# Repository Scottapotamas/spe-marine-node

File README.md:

# Underwater Sensor Node with Single Pair Ethernet
Prototype project to build a underwater sensor node, powered by and communicating with the surface via Single Pair Ethernet (10BASE-T1L + 802.3cg Type E Class 10-12).

A more detailed write-up can be [read on Electric UI's blog](https://electricui.com/blog/spe-sensor-node).

# Mechanical

## Housing

The body of the sensor node is a 2″ acrylic tube (*~58mm OD*), with a pair of aluminium end-caps. This provides a working volume constrained by the 50 mm internal diameter and ~118 mm maximum gap between caps.

The top cap/bulkhead has 4×M10 threaded holes for accessories as part of BlueRobotic's hardware ecosystem. The assembled prototype is fitted with:

- 4.5mm Wetlink penetrator for the tether cable
- 10m rated pressure sensor
- White indicator LED
- Pressure relief/test valve

Whilst this prototype won't see properly deep water, this tube arrangement should be capable of  200m operation, and far deeper if an aluminium sleeve is used.

CAD models and assemblies are in `/mechanical/tube/`. Off-the-shelf parts are in `/mechanical/tube/cots/`.

## Internal brackets

A pair of 3D printed board mounts use the 4×M3 internal mounting holes in the bulkheads.

CAD models and STL files are in `/mechanical/tube/`. 

## Mounting

The tube itself doesn't have any features for mounting, so a pair of custom tube clamps were printed with the general goal of providing generic strap or wire mounting points. 

Files are in `/mechanical/mount/`.

# Electronics

Compatibility with the [Sparkfun MicroMod ecosystem](https://www.sparkfun.com/micromod) has been maintained where possible - building off of [Sparkfun's ADIN1110 function board](https://www.sparkfun.com/products/19038) for bring-up and early software tests.

PCB's were designed with KiCAD 7. Project files, gerbers and schematic PDF's are in `/electronics/`.

A small collection of calculator spreadsheets were made to help during the design process - these are in `/docs` and use Open Office `.ods` format.

Version 1.0 boards do have some minor issues which were tweaked during bench testing, so I'd recommend reviewing things thorough before copying anything into your designs.

## Backplane

Acting as the MicroMod 'carrier', providing the processor and function board connections, as well as regulation, I2C headers, and breakout pads for spare/conflicted IO. It also serves as the mounting interface for sensor payloads and custom hardware. 

It's a 46×100 mm 1.6 mm 2-layer board with pretty relaxed fabrication requirements. 

## PD and PSE Function Boards

Both boards implement the ADIN1110 SPE transceiver in a similar manner to Sparkfun's function board, but exist as two variants which improve over the dev-kit by adding:

- Circuitry to act as a Class 10-12 PoDL **power supply** aka PSE (pictured below on left).

- VID circuitry to signal compliance as a Class 10-12 PoDL **powered device** aka PD (pictured on right).

> These boards only provide detection, not classification via SCCP, and as such runs in 'fast-start mode'.

The PCB's are A×B mm, 0.8mm thick, 2-layer boards which can be manufactured with commodity fabs. I just used the raw straight PCB edge-connector without issues, but for best practice and/or frequent insertion cycles the edge-connector should be bevelled.

The blog post describes PoDL circuit behaviour and integration in more detail.

## Sensors

The project was designed without assuming any specific sensors would be used, but I used these I2C sensors:

- Temperature & Humidity - `SHTC3` via [Sparkfun `SEN-16467`](https://www.sparkfun.com/products/16467)
- Motion - `LSM6DSO` via [Sparkfun `SEN-18020`](https://www.sparkfun.com/products/18020)
- Depth/Pressure - `MS5837` via [BlueRobotics `Bar02`](https://bluerobotics.com/store/sensors-cameras/sensors/bar02-sensor-r1-rp/)

# Firmware

I used an ESP32 MicroMod processor board along with the Arduino toolchain. As such, there are external dependencies on the ESP32 Arduino core, [`electricui-embedded`](https://github.com/electricui/electricui-embedded), and Sparkfun packages for their [ESP32 boards](https://github.com/sparkfun/Arduino_Boards), [`LSM6DS0`](https://github.com/sparkfun/SparkFun_Qwiic_6DoF_LSM6DSO), [`SHTC3`](https://github.com/sparkfun/SparkFun_SHTC3_Arduino_Library) and [`ADIN1110`](https://github.com/sparkfun/SparkFun_ADIN1110_Arduino_Library) libraries.

I also depend on my own [`MS5837`](https://github.com/Scottapotamas/MS5837) library (external to this repo) for working with the pressure sensor.

The `/firmware` folder has some of the test-sketches written during testing:

- `spe-pse-io` - Bench-test PoDL PSE behaviour with a simple state-machine
- `lsm6ds0-fifo-test` - Configures and reads IMU samples periodically from the buffer
- `led-io-test` - Rough test using Pololu's APA102 library to check the 2×24 LED rings
- `spe-eui-bridge` - Transparent proxy of `electricui-embedded` packets with ADIN1110 raw buffers to serial ports.

> These sketches weren't written to act as examples or as reference material, and should be treated accordingly.

The main firmware is actually rather straightforward, running a superloop which runs each sub-system at a defined rate. Sub-systems never block, and are generally only responsible for their own behaviour. 

> **TODO: Cleanup and merge branches/sources into this repo**

# User Interface

> **TODO: Cleanup and merge sources into this repo**

The user interface is built with [Electric UI](https://electricui.com), and can be built and run by invoking `arc start` from `/interface`.

It handles visualisation of data streaming off the sensor node, and provides additional statistics and logging.

**TODO: Write part 2 post on data processing and visualisation**

# Additional Notes

_If_ you're planning on replicating this project, or part of it, some additional points of interest:

- I'm happy to answer questions or help with design changes to suit your ocean research project.
  - I'm also generally open to consulting work!
- Firmware is pretty specific to my own tooling and relies on external libraries for sensors and the Arduino ESP32 core.
- Read over BlueRobotics's guides for Wetlink penetrator use, enclosure assembly, pressure testing.
  - Definitely do remember to lubricate o-rings and the tube bulkheads as you slide them into the cylinder. It's _very difficult_ to get them out dry... 
- The tube *as designed and pictured* is positively buoyant and might need additional ballast weight depending on your application and safety requirements around handling.

Its also worth mentioning that the entire detailed conceptualisation, design, ordering, assembly, testing and writeup occurred in August 2023. There were many late nights, and as a result some design choices were made with simplicity or time-frame in mind.

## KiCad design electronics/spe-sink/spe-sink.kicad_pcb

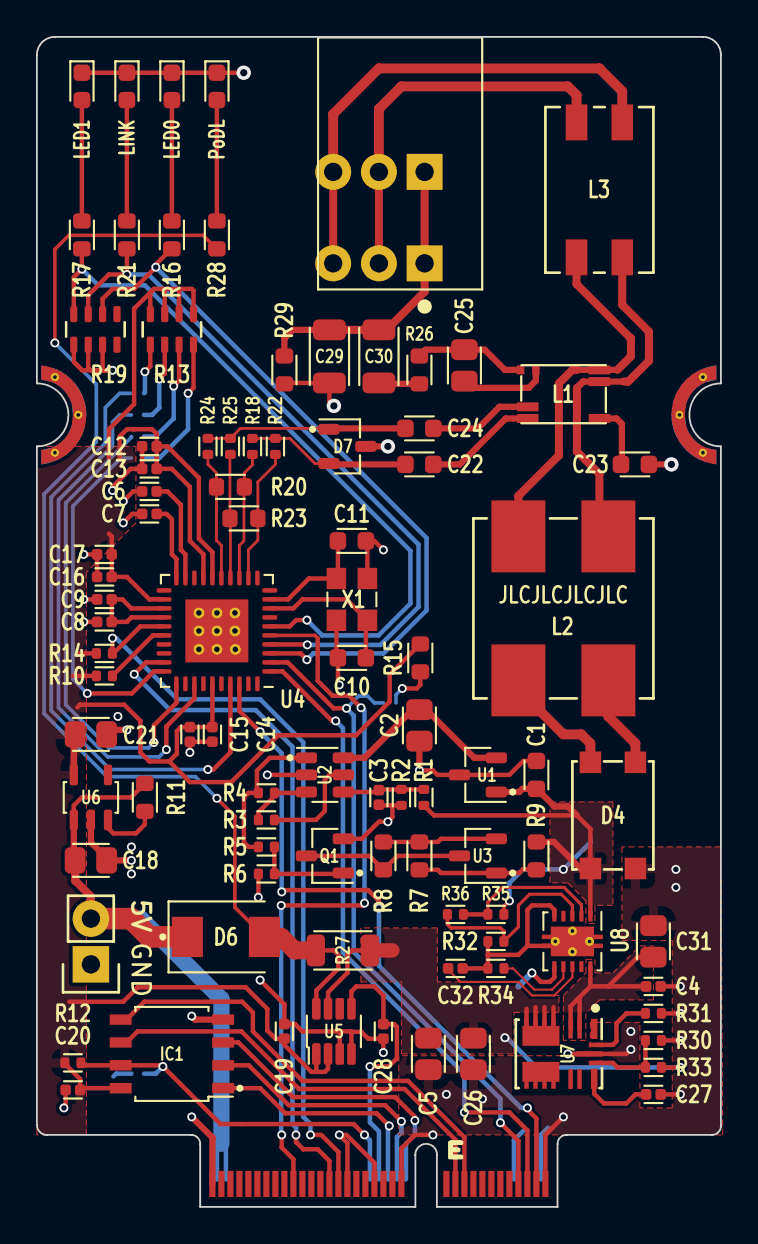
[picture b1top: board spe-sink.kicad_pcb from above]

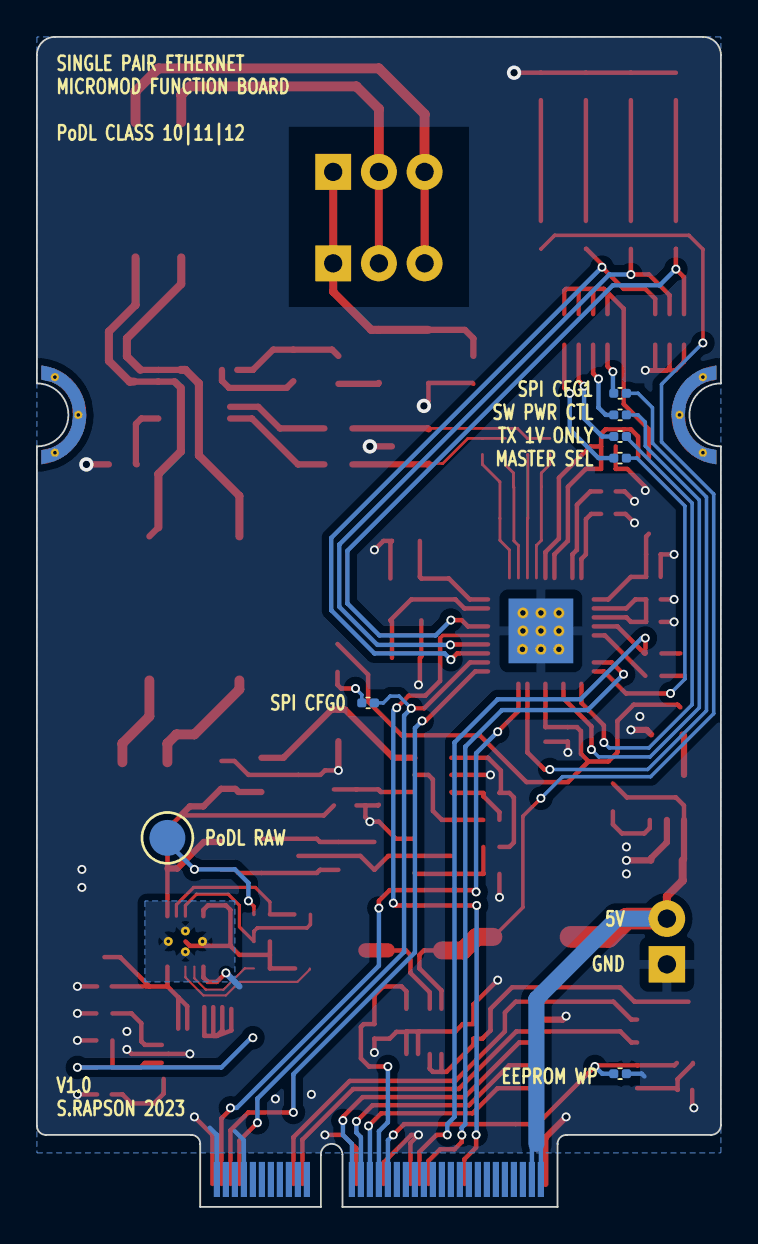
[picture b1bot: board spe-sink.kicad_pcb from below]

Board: 2 copper layers, 38.0 x 65.0 mm, 99 parts (7 on the bottom side), 79 nets.

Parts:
C1: 56n_X7R_1608M; CAPC1608X90N
C2, C18, C21: 10u_X7R_2012M; CAPC2012X110N
C3: 330p_X7R_1005M; CAPC1005X60N
C4, C6, C8, C12, C14, C16, C19, C20: 100n_X7R_1005M; CAPC1005X60N
C5, C26: 22u_X5R_2012M; CAPC2012X110N
C7, C27: 1u_X5R_1005M; CAPC1005X60N
C9: 470n_X5R_1005M; CAPC1005X60N
C10, C11: 22p_X7R_1608M; CAPC1608X90N
C13, C15, C17, C32: 10n_X7R_1005M; CAPC1005X60N
C22, C24: 220n_X7R_1608M; CAPC1608X90N
C23: 100n_X7R_1608M; CAPC1608X90N
C25: 470n_X7R_2012M_100V; CAPC2012X110N
C28: 1n_X7R_1005M; CAPC1005X60N
C29, C30: 1n_X7R_3216M_2kV; CAPC3216X135N
C31: 10u_X5R_2012M_50V; CAPC2012X110N
D1: LED_GREEN_1608M; LEDC1608X80L40N
D2: LED_YELLOW_1608M; LEDC1608X80L40N
D3: LED_BLUE_1608M; LEDC1608X80L40N
D4: CD-HD2006L; CD-HD2x(L)
D5: LED_RED_1608M; LEDC1608X80L40N
D6: B240Q-13-F; SODFL5436X262N
D7: D1213A; SOT95P240X110-3L16N
IC1: AT24C02C-SSHM; SOIC127P600X330-8L2N
J1: CONN_01X05_RA; CUI_TBL009-254-03
L1: WE-STST_74930000; WE-STST
L2: COUPLED_47uH_1500mA_340mOhm; WE-MCRI-1040
L3: COMM_MODE_1000uH_800mA_0.3R; WE-SL2
P2: CONN_01X02; 61300211121
Q1: 2N7002P; SOT95P240X110-3L16N
R1: 1M_1005M; RESC1005X40N
R2, R4: 470K_1005M; RESC1005X40N
R3, R6, R30: 10K0_1005M; RESC1005X40N
R5: 0R_1005M; RESC1005X40N
R7: 9K09_1608M; RESC1608X50N
R8: 20K0_1608M; RESC1608X50N
R9: 22R_1608M; RESC1608X50N
R10, R14: 1K5_1005M; RESC1005X40N
R11: 10K0_1608M; RESC1608X50N
R12: 100K_1005M; RESC1005X40N
R13, R19: 4K7_QUAD_ARRAY_1608M; R_Array_Concave_4x1608M
R15: 4K7_1608M; RESC1608X50N
R16, R21, R28: 1K00_1608M; RESC1608X50N
R17: 2K40_1608M; RESC1608X50N
R18, R25: 5K1_1005M; RESC1005X40N
R20, R23: 10K2_1608M; RESC1608X50N
R22, R24: 49R9_1005M; RESC1005X40N
R26: 100R_1608M; RESC1608X50N
R27: R01_3216M; RESC3216X60N
R29: 1M_1608M; RESC1608X50N
R31: 15K_1005M; RESC1005X40N
R32: 26K1_1005M; RESC1005X40N
R33: 40K2_1005M; RESC1005X40N
R34: 13K_1005M; RESC1005X40N
R35: 680K_1005M; RESC1005X40N
R36: 36K_1005M; RESC1005X40N
SL2, SL3, SL4, SL5, SL6, SL7: SOLDER-LINK-2-TINY; SJ1005-2N
TEST1: PROBE_PAD; TP200
U1: AP7375-33; SOT95P240X110-3L16N
U2: MCP65R41T; SOT95P240X110-6L16N
U3: ATL431LIB; SOT95P240X110-3L16N
U4: ADIN1110; QFN50P600X600X100-40T350X350N
U5: INA186A3; SOT23-8P65_280X145L45X30N
U6: AP2112K-3.3; SOT95P280X145-5L30N
U7: TLVM23625RDNR; QFN50P450X350X200-11-FCMOD11
U8: TPS26625; SON50P300X300X90-11T240X165N_RELIEF
X1: RH100-25.000-13-F-0715; OSCCC320X250X60L90X100N
X2: MICROMOD_FUNCTION_BOARD_EDGE; M.2-MICROMOD-FN-CARD-EDGE

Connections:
+3.3V: C12.1, C13.1, C14.1, C15.1, C16.1, C17.1, C19.1, C20.1, C21.1, IC1.8 (VCC), R10.1, R12.1, R13.1, R13.2, R13.3, R13.4, R14.1, R15.1, U4.16 (AVDD_H), U4.17 (AVDD_H), U4.22 (AVDD_L), U4.35 (VDDIO), U5.1 (VCC), U5.2 (EN), U6.5 (VOUT)
+POWER: C18.1, D6.C, P2.2, R11.1, U6.1 (VIN), X2.72 (VCC), X2.74 (VCC)
/Ethernet MAC+PHY/CIPO: SL4.1, U4.2 (SDO/SPI_CFG0), X2.7 (SPI_SDO)
/Ethernet MAC+PHY/CLK: U4.38 (SCLK), X2.3 (SPI_SCK)
/Ethernet MAC+PHY/COPI: U4.1 (SDI), X2.5 (SPI_SDI)
/Ethernet MAC+PHY/DATA+: C24.2, D7.1 (A1), R24.1, R25.1
/Ethernet MAC+PHY/DATA-: C22.2, D7.2 (C2), R18.1, R22.1
/Ethernet MAC+PHY/~CS: U4.29 (~CS), X2.49 (F1/~CS)
/Ethernet MAC+PHY/~INT: R14.2, U4.25 (~INT), X2.47 (F0/~INT)
/Ethernet MAC+PHY/~RESET: U4.5 (~RESET), X2.57 (F5)
/MicroMod Function Board/ANALOG: C28.1, U5.5 (Vout), X2.38 (A0)
/MicroMod Function Board/SCL: IC1.6 (SCL), X2.21 (I2C_SCL)
/MicroMod Function Board/SDA: IC1.5 (SDA), X2.19 (I2C_SDA)
/PoDL Device Handling/PoDL+: C1.1, D4.1 (+), R1.1, R9.1, R35.1, TEST1.1 (PAD), U1.1 (VIN), U8.1 (IN)
Earth: C29.2, C30.1, J1.1, R29.1
GND: C1.2, C2.2, C3.2, C4.2, C5.2, C6.2, C7.2, C8.2, C9.2, C10.2, C11.2, C12.2, C13.2, C14.2, C15.2, C16.2, C17.2, C18.2, C19.2, C20.2, C21.2, C23.2, C26.2, C27.2, C28.2, C30.2, C31.2, D1.C, D2.C, D3.C, D4.4 (-), D5.C, D7.3, IC1.4 (GND), P2.1, Q1.2 (S), R2.2, R6.2, R19.1, R19.2, R19.3, R29.2, R30.2, R31.2, SL2.2, U1.3 (GND), U2.2 (V-), U4.41 (EP(GND)), U5.3 (REF), U5.4 (GND), U6.2 (GND), U7.10 (GND), U8.6 (GND), X1.2, X1.4, X2.1 (GND), X2.2 (GND), X2.8 (GND), X2.33 (GND), X2.39 (GND), X2.45 (GND), X2.75 (GND)
unnamed: C22.1, L1.1
unnamed: C23.1, L1.5
unnamed: C24.1, L1.2
unnamed: C25.1, L1.4
unnamed: C25.2, L1.3, R26.1
unnamed: C29.1, R26.2
unnamed: D1.A, R16.1
unnamed: D2.A, R17.1
unnamed: D3.A, R21.1
unnamed: D4.2 (∿), L2.4
unnamed: D4.3 (∿), L2.1
unnamed: D5.A, R28.2
unnamed: IC1.1 (A0), X2.36 (EEPROM_A0)
unnamed: IC1.2 (A1), X2.34 (EEPROM_A1)
unnamed: IC1.3 (A2), X2.32 (EEPROM_A2)
unnamed: IC1.7 (WP), R12.2, SL2.1, X2.40 (EEPROM_WP)
unnamed: J1.2, L3.2
unnamed: J1.3, L3.1
unnamed: L1.6, L2.2, L3.4
unnamed: L1.7, L2.3, L3.3
unnamed: Q1.3 (D), R8.2, U3.3 (A)
unnamed: Q1.1 (G), R5.2, R6.1
unnamed: R4.2, R5.1, U2.1
unnamed: R13.5, SL3.2
unnamed: R13.6, SL6.2
unnamed: R13.7, SL7.2
unnamed: R13.8, SL5.2
unnamed: R15.2, SL4.2
unnamed: C2.1, U1.2 (VOUT), U2.6 (V+)
unnamed: R3.2, R4.1, U2.3 (+)
unnamed: C3.1, R1.2, R2.1, U2.4 (-)
unnamed: R3.1, U2.5 (REF)
unnamed: R7.1, R9.2, U3.1 (C)
unnamed: R7.2, R8.1, U3.2 (REF)
unnamed: C6.1, U4.19 (CEXT_2)
unnamed: C7.1, U4.20 (CEXT_3)
unnamed: C8.1, C9.1, U4.23 (DLDO_1P1), U4.24 (DVDD_1P1)
unnamed: R16.2, R19.6, U4.3 (LED_0)
unnamed: R17.2, R19.8, U4.6 (LED_1)
unnamed: R19.7, R21.2, U4.4 (LINK_ST)
unnamed: R18.2, R20.1, U4.13 (RXN)
unnamed: R23.2, R25.2, U4.14 (RXP)
unnamed: SL3.1, U4.37 (SPI_CFG1)
unnamed: R10.2, U4.26 (TEST1)
unnamed: SL5.1, U4.30 (TS_TIMER/MS_SEL)
unnamed: R22.2, R23.1, U4.12 (TXN)
unnamed: R20.2, R24.2, U4.15 (TXP)
unnamed: C10.1, U4.8 (XTAL_I/CLK_IN), X1.3
unnamed: C11.1, U4.9 (XTAL_O), X1.1
unnamed: SL6.1, U4.33 (~SWPD_EN)
unnamed: SL7.1, U4.31 (~TX2P4_EN)
unnamed: C5.1, C26.1, R27.1, R33.1, U5.7 (S+), U7.4 (VOUT)
unnamed: D6.A, R27.2, R28.1, U5.8 (S-)
unnamed: R11.2, U6.3 (EN)
unnamed: C4.1, C31.1, U7.2 (EN), U7.3 (VIN), U8.10 (OUT)
unnamed: R30.1, R33.2, U7.9 (FB)
unnamed: R31.1, U7.11 (RT)
unnamed: C27.1, U7.8 (VCC)
unnamed: C32.2, R32.2, R34.2, U8.5 (RTN), U8.11 (EP)
unnamed: R34.1, U8.7 (ILIM)
unnamed: R32.1, R36.2, U8.3 (OVP)
unnamed: R35.2, R36.1, U8.2 (ULVO)
unnamed: C32.1, U8.8 (dVdT)

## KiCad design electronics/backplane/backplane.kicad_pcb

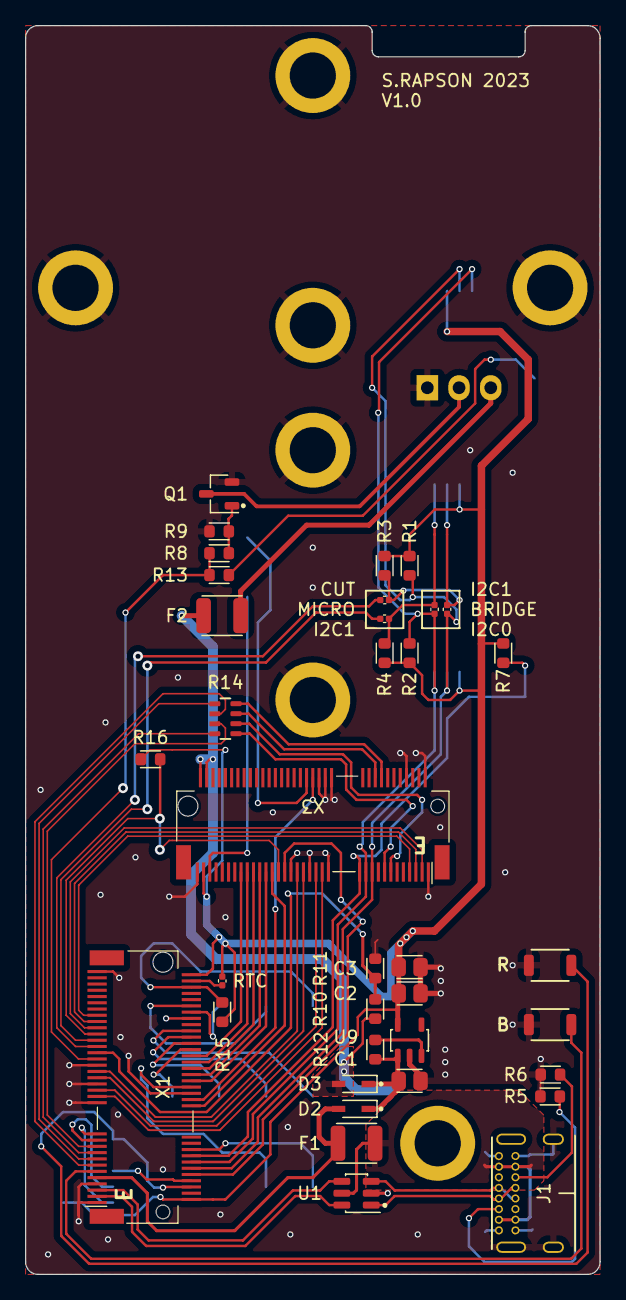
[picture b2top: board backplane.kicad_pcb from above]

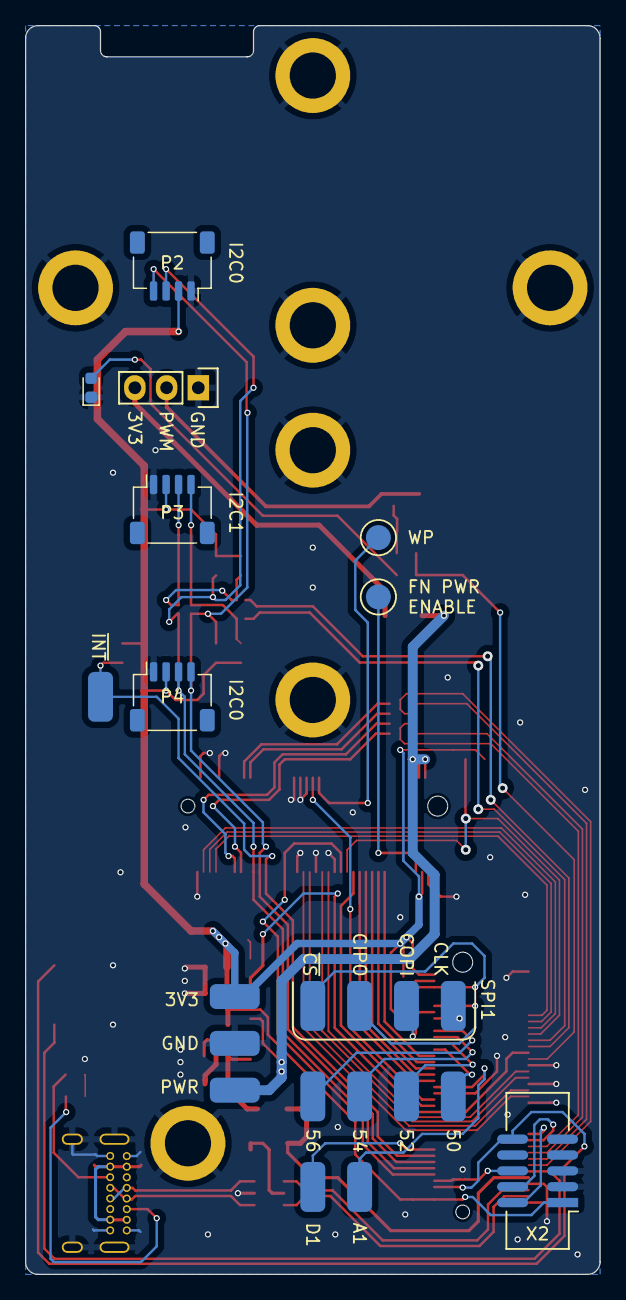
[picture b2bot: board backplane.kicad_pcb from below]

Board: 2 copper layers, 46.0 x 100.0 mm, 65 parts (26 on the bottom side), 68 nets.

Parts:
C1, C2, C3: 10u_X7R_2012M; CAPC2012X110N
D1: LED_YELLOW_1608M; LEDC1608X80L40N
D2, D3: 40V_500mA_SOD323; SOD2512X110N
F1, F2: 0.5A_1210L_PTC; FUSC3225X85L50N
J1: USB_C_SOCKET_RA_PTH_SIMPLE; USB_C_PTH_GCT_USB4085
MNT1, MNT2, MNT3: M2.5_SMD_2.5MM_THREADED; 9774025151R
MNT4, MNT5, MNT6, MNT7: M2.5_SMD_4.0MM_THREADED; 9774040151R
P1, P5, P6, P7, P8, P9, P11, P12, P13, P14, P15, P16, P17, P18: PAD_SOLDER_2mm
P2, P3, P4: JST_SH_4_RA; SM04B-SRSS-TB
P10: CONN_01X03; 61300311121
Q1: 2N7002P; SOT95P240X110-3L16N
R1, R2, R3, R4: 4K7_1608M; RESC1608X50N
R5, R6: 4K99_1608M; RESC1608X50N
R7, R9, R11, R12: 10K0_1608M; RESC1608X50N
R8: 10R_1608M; RESC1608X50N
R10: 20K0_1608M; RESC1608X50N
R13: 1K00_1608M; RESC1608X50N
R14: 0R_QUAD_ARRAY_1608M; R_Array_Concave_4x1608M
R15, R16: 100K_1608M; RESC1608X50N
SL1, SL4, SL5, SL6, SL7: SOLDER-LINK-2-TINY; SJ1005-2N
SW1, SW2: B3U-1000P_SPST-NO_SMD; B3U-1000P
TEST1, TEST2: PROBE_PAD; TP200
U1: USBLC6; SOT95P280X145-6L50N
U9: AP2112K-3.3; SOT95P280X145-5L30N
X1: MICROMOD_PROCESSOR_SOCKET; TE_2199230-4
X2: SWD_SMT_SOCKET; CNCTECH_3220-10-0300-00
X3: MICROMOD_FUNCTION_BOARD_SOCKET; TE_2199230-4

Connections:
+3.3V: C2.1, C3.1, P2.2, P3.2, P4.2, P15.1, R1.1, R2.1, R3.1, R4.1, R7.1, R15.1, R16.1, SL1.2, U9.5 (VOUT), X1.2 (3V3), X1.74 (3V3), X2.1 (VTref), X3.73 (3V3)
+POWER: D3.A, F2.1, P5.1, R10.1, X3.72 (VCC), X3.74 (VCC)
/Expansion IO/ANALOG_IN: P18.1, X1.38 (A1)
/Expansion IO/CIPO: P12.1, X1.64 (SPI_CIPO1/SDIO_DATA0)
/Expansion IO/CLK: P11.1, X1.60 (SPI_SCK1/SDIO_CLK)
/Expansion IO/COPI: P13.1, X1.62 (SPI_COPI1/SDIO_CMD)
/Expansion IO/DIGITAL_OUT: P17.1, X1.18 (D1/CAM_TRIG)
/Expansion IO/I2C0.SCL: P2.4, P4.4, R2.2, SL6.1, X1.14 (I2C_SCL), X3.21 (I2C_SCL)
/Expansion IO/I2C0.SDA: P2.3, P4.3, R1.2, SL7.2, X1.12 (I2C_SDA), X3.19 (I2C_SDA)
/Expansion IO/I2C1.SCL: P3.4, R4.2, SL5.1, SL6.2
/Expansion IO/I2C1.SDA: P3.3, R3.2, SL4.1, SL7.1
/Expansion IO/PWM_OUTPUT: R8.1, R13.2, X1.47 (PWM1)
/Expansion IO/~CS: P14.1, R15.2, X1.70 (~SPI_CS1/SDIO_DATA3)
/Expansion IO/~I2C_INT: P1.1, R7.2, X1.16 (~I2C_INT), X3.23 (~I2C_INT)
/Function Board/CAN.RX: X1.41 (CAN_RX), X3.41 (CAN_TX)
/Function Board/CAN.TX: X1.43 (CAN_TX), X3.43 (CAN_RX)
/Function Board/CIPO: X1.61 (SPI_CIPO), X3.7 (SPI_SDO)
/Function Board/CLK: X1.57 (SPI_SCK), X3.3 (SPI_SCK)
/Function Board/COPI: X1.59 (SPI_COPI), X3.5 (SPI_SDI)
/Function Board/CTS: R14.5, X1.15 (UARTCTS1)
/Function Board/D+: X1.35 (USBHOST_D+), X3.35 (USBHOST_D+)
/Function Board/D-: X1.37 (USBHOST_D-), X3.37 (USBHOST_D-)
/Function Board/FN_ANALOG: X1.34 (A0), X3.38 (A0)
/Function Board/FN_PWM: X1.32 (PWM0), X3.51 (F2/PWM)
/Function Board/FN_~INT: X1.10 (D0), X3.47 (F0/~INT)
/Function Board/G0: X1.40 (G0/BUS0), X3.53 (F3)
/Function Board/G1: X1.42 (G1/BUS1), X3.55 (F4)
/Function Board/G2: X1.44 (G2/BUS2), X3.57 (F5)
/Function Board/G3: X1.46 (G3/BUS3), X3.59 (F6)
/Function Board/G4: X1.48 (G4/BUS4), X3.61 (F7)
/Function Board/RTS: R14.6, X1.13 (UART_RTS1)
/Function Board/RX: R14.7, X1.19 (UART_RX1)
/Function Board/TX: R14.8, X1.17 (UART_TX1)
/Function Board/~CS: R16.2, X1.55 (~SPI_CS), X3.49 (F1/~CS)
/Power Regulation/USB_VCC: D2.A, F1.2, X1.9 (USB_VIN)
/Processor/NATIVE.D+: U1.6 (OUT_1), X1.3 (USB_D+)
/Processor/NATIVE.D-: U1.4 (OUT_2), X1.5 (USB_D-)
/Processor/SWDCLK: X1.21 (SWDCLK), X2.4 (SWCLK)
/Processor/SWDIO: X1.23 (SWDIO), X2.2 (SWDIO)
/Processor/SWO: X1.8 (G11/SWDSWO), X2.6 (SWO)
/Processor/~BOOT: SW2.1, X1.11 (BOOT)
/Processor/~RESET: SW1.1, X1.6 (~RESET), X2.10 (~RESET)
/USB Input/USBC_N: J1.A7 (D-), J1.B7 (D-), U1.3 (IN_2)
/USB Input/USBC_P: J1.A6 (D+), J1.B6 (D+), U1.1 (IN_1)
GND: C1.2, C2.2, C3.2, D1.C, J1.A1 (GND), J1.A12 (GND), J1.B1 (GND), J1.B12 (GND), J1.S1 (Shield), MNT1.1, MNT2.1, MNT3.1, MNT4.1, MNT5.1, MNT6.1, MNT7.1, P2.1, P3.1, P4.1, P10.1, P16.1, Q1.2 (S), R5.2, R6.2, R9.2, R11.2, SW1.2, SW2.2, U1.2 (GND), U9.2 (GND), X1.1 (GND), X1.7 (GND), X1.33 (GND), X1.36 (GND), X1.39 (GND), X1.45 (GND), X1.75 (GND), X2.3 (Gnd), X2.5 (Gnd), X3.1 (GND), X3.2 (GND), X3.8 (GND), X3.32 (EEPROM_A2), X3.33 (GND), X3.34 (EEPROM_A1), X3.36 (EEPROM_A0), X3.39 (GND), X3.45 (GND), X3.75 (GND)
unnamed: D1.A, R13.1
unnamed: J1.A5 (CC1), R5.1
unnamed: J1.B5 (CC2), R6.1
unnamed: P6.1, X1.56 (AUD_OUT/PCM_OUT/I2S_OUT/CAM_MCLK)
unnamed: P7.1, X1.54 (AUD_IN/PCM_IN/I2S_IN/CAM_PCLK)
unnamed: P8.1, X1.52 (AUD_LRCLK/PCM_SYNC/I2S_WS/PDM_DATA)
unnamed: P9.1, X1.50 (AUD_BCLK/PCM_CLK/I2S_SCK/PDM_CLK)
unnamed: P10.2, Q1.3 (D)
unnamed: F2.2, P10.3
unnamed: Q1.1 (G), R8.2, R9.1
unnamed: TEST1.1 (PAD), X3.71 (PWR_EN)
unnamed: TEST2.1 (PAD), X3.40 (EEPROM_WP)
unnamed: F1.1, J1.A4 (VBUS), J1.A9 (VBUS), J1.B4 (VBUS), J1.B9 (VBUS), U1.5 (VBUS)
unnamed: R12.2, U9.3 (EN)
unnamed: C1.1, D2.C, D3.C, R12.1, U9.1 (VIN)
unnamed: R10.2, R11.1, X1.49 (BATT_VIN/3)
unnamed: SL5.2, X1.53 (I2C_SCL1)
unnamed: SL4.2, X1.51 (I2C_SDA1)
unnamed: SL1.1, X1.72 (RTC_3V_BATT)
unnamed: R14.3, X3.18 (FUNC_CTS)
unnamed: R14.4, X3.16 (FUNC_RTS)
unnamed: R14.1, X3.15 (FUNC_RX)
unnamed: R14.2, X3.13 (FUNC_TX)

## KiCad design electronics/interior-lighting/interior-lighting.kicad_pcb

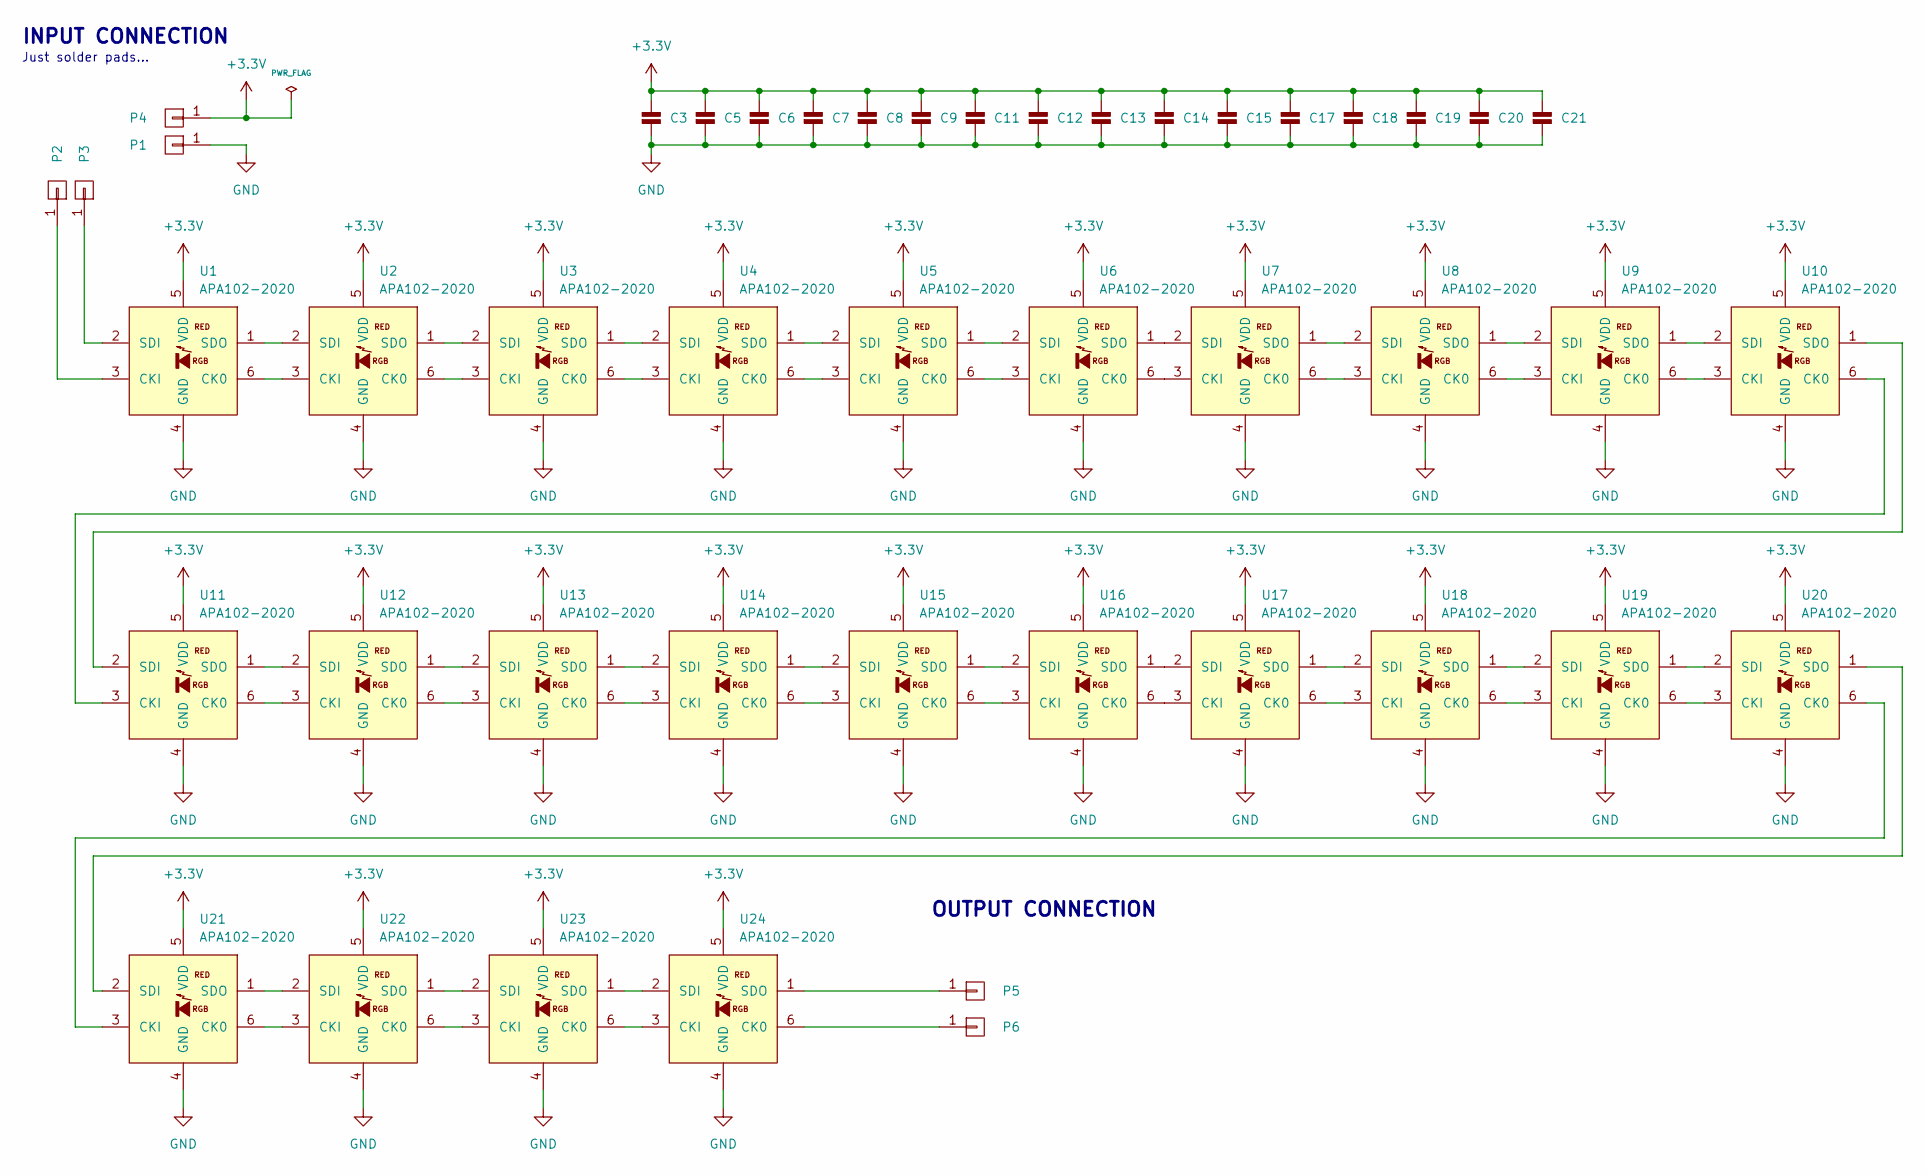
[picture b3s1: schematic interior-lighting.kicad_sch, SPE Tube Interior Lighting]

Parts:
C3, C5, C6, C7, C8, C9, C11, C12, C13, C14, C15, C17, C18, C19, C20, C21: 100n_X7R_1608M; CAPC1608X90L
P1, P2, P3, P4, P5, P6: PAD_SOLDER_2mm; PAD_SOLDER_2mm_SQUARE
U1, U2, U3, U4, U5, U6, U7, U8, U9, U10, U11, U12, U13, U14, U15, U16, U17, U18, U19, U20, U21, U22, U23, U24: APA102-2020; AP102_200X200X90L

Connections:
+3.3V: C3.1, C5.1, C6.1, C7.1, C8.1, C9.1, C11.1, C12.1, C13.1, C14.1, C15.1, C17.1, C18.1, C19.1, C20.1, C21.1, P4.1, U1.5 (VDD), U2.5 (VDD), U3.5 (VDD), U4.5 (VDD), U5.5 (VDD), U6.5 (VDD), U7.5 (VDD), U8.5 (VDD), U9.5 (VDD), U10.5 (VDD), U11.5 (VDD), U12.5 (VDD), U13.5 (VDD), U14.5 (VDD), U15.5 (VDD), U16.5 (VDD), U17.5 (VDD), U18.5 (VDD), U19.5 (VDD), U20.5 (VDD), U21.5 (VDD), U22.5 (VDD), U23.5 (VDD), U24.5 (VDD)
GND: C3.2, C5.2, C6.2, C7.2, C8.2, C9.2, C11.2, C12.2, C13.2, C14.2, C15.2, C17.2, C18.2, C19.2, C20.2, C21.2, P1.1, U1.4 (GND), U2.4 (GND), U3.4 (GND), U4.4 (GND), U5.4 (GND), U6.4 (GND), U7.4 (GND), U8.4 (GND), U9.4 (GND), U10.4 (GND), U11.4 (GND), U12.4 (GND), U13.4 (GND), U14.4 (GND), U15.4 (GND), U16.4 (GND), U17.4 (GND), U18.4 (GND), U19.4 (GND), U20.4 (GND), U21.4 (GND), U22.4 (GND), U23.4 (GND), U24.4 (GND)
unnamed: P2.1, U1.3 (CKI)
unnamed: P3.1, U1.2 (SDI)
unnamed: P5.1, U24.1 (SDO)
unnamed: P6.1, U24.6 (CK0)
unnamed: U1.6 (CK0), U2.3 (CKI)
unnamed: U1.1 (SDO), U2.2 (SDI)
unnamed: U2.6 (CK0), U3.3 (CKI)
unnamed: U2.1 (SDO), U3.2 (SDI)
unnamed: U3.6 (CK0), U4.3 (CKI)
unnamed: U3.1 (SDO), U4.2 (SDI)
unnamed: U4.6 (CK0), U5.3 (CKI)
unnamed: U4.1 (SDO), U5.2 (SDI)
unnamed: U5.6 (CK0), U6.3 (CKI)
unnamed: U5.1 (SDO), U6.2 (SDI)
unnamed: U6.6 (CK0), U7.3 (CKI)
unnamed: U6.1 (SDO), U7.2 (SDI)
unnamed: U7.6 (CK0), U8.3 (CKI)
unnamed: U7.1 (SDO), U8.2 (SDI)
unnamed: U8.6 (CK0), U9.3 (CKI)
unnamed: U8.1 (SDO), U9.2 (SDI)
unnamed: U10.6 (CK0), U11.3 (CKI)
unnamed: U9.6 (CK0), U10.3 (CKI)
unnamed: U9.1 (SDO), U10.2 (SDI)
unnamed: U10.1 (SDO), U11.2 (SDI)
unnamed: U11.6 (CK0), U12.3 (CKI)
unnamed: U11.1 (SDO), U12.2 (SDI)
unnamed: U12.6 (CK0), U13.3 (CKI)
unnamed: U12.1 (SDO), U13.2 (SDI)
unnamed: U13.6 (CK0), U14.3 (CKI)
unnamed: U13.1 (SDO), U14.2 (SDI)
unnamed: U14.6 (CK0), U15.3 (CKI)
unnamed: U14.1 (SDO), U15.2 (SDI)
unnamed: U15.6 (CK0), U16.3 (CKI)
unnamed: U15.1 (SDO), U16.2 (SDI)
unnamed: U16.6 (CK0), U17.3 (CKI)
unnamed: U16.1 (SDO), U17.2 (SDI)
unnamed: U17.6 (CK0), U18.3 (CKI)
unnamed: U17.1 (SDO), U18.2 (SDI)
unnamed: U18.6 (CK0), U19.3 (CKI)
unnamed: U18.1 (SDO), U19.2 (SDI)
unnamed: U19.6 (CK0), U20.3 (CKI)
unnamed: U19.1 (SDO), U20.2 (SDI)
unnamed: U20.6 (CK0), U21.3 (CKI)
unnamed: U20.1 (SDO), U21.2 (SDI)
unnamed: U21.6 (CK0), U22.3 (CKI)
unnamed: U21.1 (SDO), U22.2 (SDI)
unnamed: U22.6 (CK0), U23.3 (CKI)
unnamed: U22.1 (SDO), U23.2 (SDI)
unnamed: U23.6 (CK0), U24.3 (CKI)
unnamed: U23.1 (SDO), U24.2 (SDI)

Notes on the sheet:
OUTPUT CONNECTION
Just solder pads...
INPUT CONNECTION

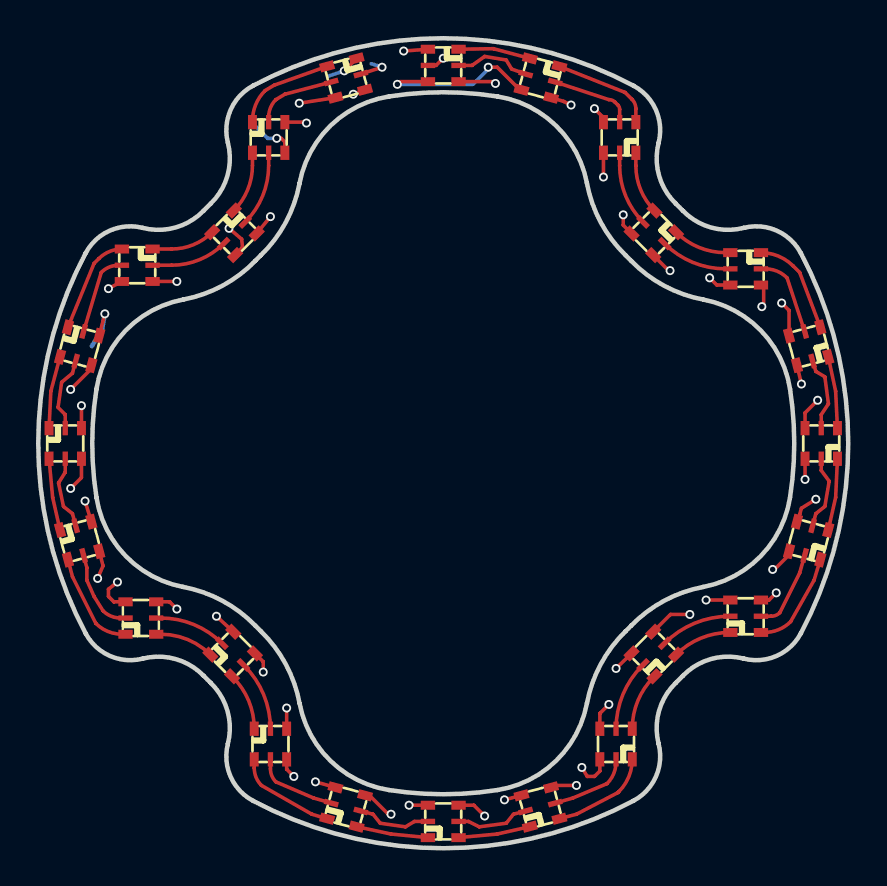
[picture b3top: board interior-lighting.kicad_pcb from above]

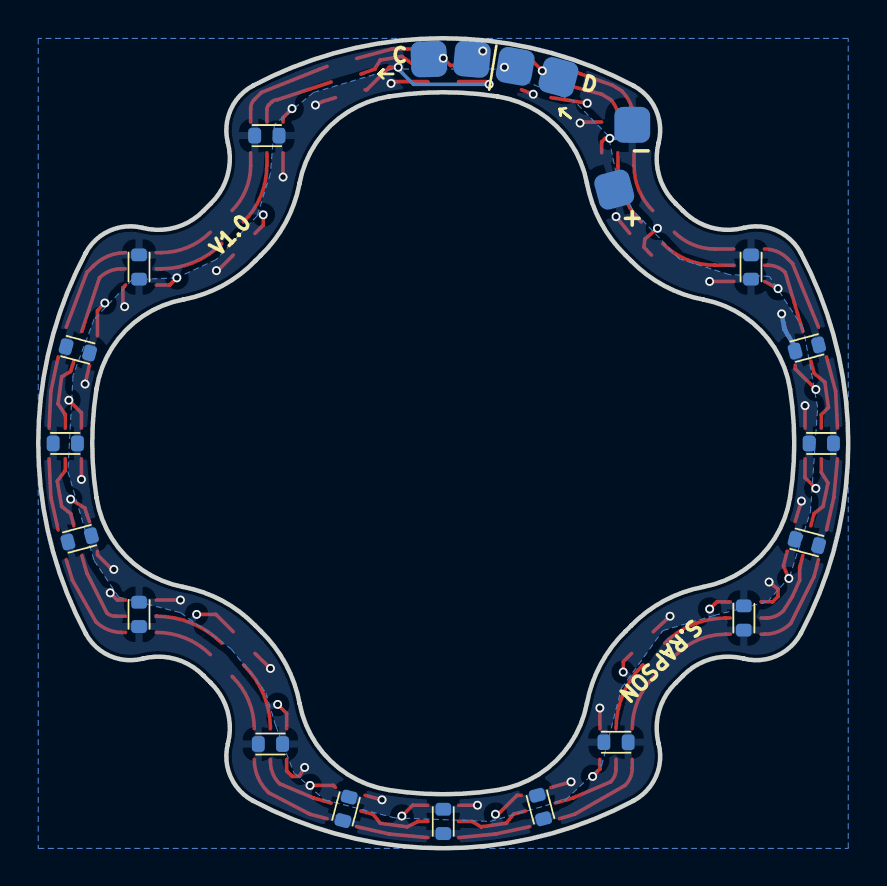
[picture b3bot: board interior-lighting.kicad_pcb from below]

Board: 2 copper layers, 45.0 x 45.0 mm, 46 parts (22 on the bottom side), 52 nets.

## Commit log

2023-07-26 First pass waterproofed tube concept
2023-07-26 Rough buoyancy calcs
    Attempt to work out positive or negative buoyancy, weight budget.
2023-08-01 Rough interior lighting ring PCB
2023-08-04 Start stubbing out backplane PCB
2023-08-05 Adds PDF for 2D tube drawing
2023-08-05 Rough cad models for Sparkfun modules/boards
    Used for layout reference
2023-08-05 Tube 2D drawing
    For size/positioning reference
2023-08-06 Backplane schematic capture and PCB shape
2023-08-06 Continue backplane PCB
2023-08-07 Continue backplane
2023-08-08 Continue schematic tweaks, start routing backplane
2023-08-08 Continue backplane design Cleanup schematic, most routing and placement done
2023-08-08 Continued routing Labels, most traces, most pours
2023-08-09 Backplane routing complete General schematic cleanup, board cosmetics etc
2023-08-09 Backplane V1.0 gerbers and schematic export
2023-08-09 Internal lighting board finished
2023-08-09 Add KiCAD gitignore entries
2023-08-10 Started PD detection ID circuit
2023-08-11 Fixed backplane i2c connector 3D model/footprint linkage Also minor schematic cleanup
2023-08-11 Continue work on PD function board schematic
2023-08-11 Notes on wave height monitoring and vis TODO
2023-08-12 Add MAC+PHY, other parts to PD function board sch
2023-08-12 Building out PDoE filter/isolation, etc
2023-08-13 Drawing/detail of PCB vertical component clearances
    Needed to know if large PDoE inductors can fit in the tube
2023-08-13 Printable mounting clamp, small spacer to stop tube rolling off desk
2023-08-13 Printable PCB mounting brackets, LED ring diffuser
2023-08-14 Add basic renders of PCBs
2023-08-14 PCB schematic PDFs in git for easy access
2023-08-14 PD function board schematic progress
2023-08-15 PD function board bulk regulator, cleanup, part placement
2023-08-16 PD sink board routing, minor sch changes, etc
2023-08-16 PD sink PCB design 'finished', page cleanup, etc
2023-08-16 Start PSE schematic, detection source/validation circuit, etc
2023-08-16 Fix current amplifier part choice on PD board
2023-08-16 PSE part placement, partial routing
2023-08-16 PSE routing spaghetti complete
2023-08-17 TLV6700 window comparator calculator spreadsheet, PCB export settings
2023-08-17 V1.0 gerbers for PoDL PSE and PD boards
2023-08-17 Schematic PDFs for PSE and PD function boards
2023-08-19 Revised PSE input voltage limit resistor values
2023-08-19 Update assembly files with high detail PCB assembly
2023-08-19 PCB models imported, test assembly
2023-08-19 STL exports for internal mounting braces
2023-08-21 Readme stubs
2023-08-21 Sensor bringup/test sketches
2023-08-25 Additional docs
2023-08-26 PSE firmware to manage PD detection and powerup
2023-08-27 Minor tweaks to test firmware, LED test sketch
2023-08-28 Minor tweaks to test sketches
2023-08-28 More test sketches
2023-09-01 README update with images
2023-09-02 Random uncommitted KiCAD tweaks
